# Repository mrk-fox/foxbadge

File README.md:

# foxbadge
My Fallout Badge (@Hack Club)

by
@scharonowmark

## Project Description
The project presented in this Repository is a versatile "Hacker-Badge" which has the following features:
1. Seeeduino XIAO ESP32-C6 as the main processor
2. A 4-mechanical switch (Cherry MX) controll
3. A 1.9 inch TFT screen
4. A battery system (NO BMS! ONLY BATTERIES WITH INTEGRATED BMS ARE SAFTE TO USE)
5. Supports 2 diffrent kind of lanyards
6. A case!

## BOM  

| id | Name                           | Qty | Price |   |
|----|--------------------------------|-----|-------|---|
| 1  | PCB                            | 1   | 2$    |   |
| 2  | Seeeduino XIAO ESP32-C6        | 1   |       |   |
| 3  | 1.9 inch TFT screen (8-pin)    | 1   |       |   |
| 4  | Cherry MX Low Profile Switches | 4   |       |   |
| 5  | 3D-Printed Case                | 1   |       |   |
| 6  | LiPo Battery (3.7v)            | 1   |       |   |

# Pictures

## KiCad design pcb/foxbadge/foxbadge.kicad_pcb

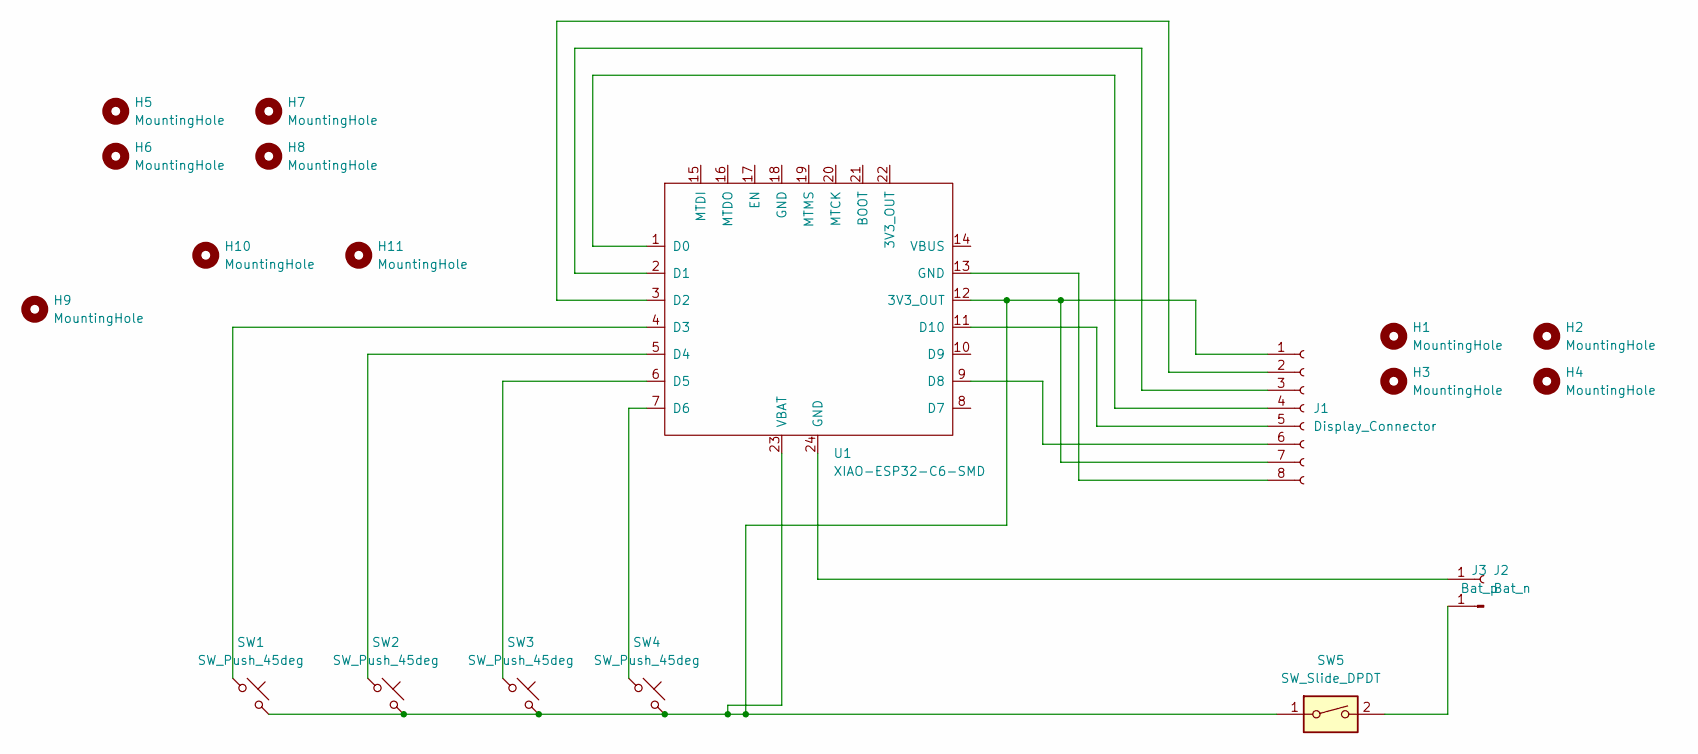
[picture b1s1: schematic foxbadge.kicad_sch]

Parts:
H1, H2, H3, H4: MountingHole; MountingHole_2.1mm
H5, H6, H7, H8: MountingHole; MountingHole_4mm
H9: MountingHole; MountingHole_6mm
H10, H11: MountingHole; MountingHole_3mm
J1: Display_Connector; PinSocket_1x08_P2.54mm_Vertical
J2: Bat_n; PinSocket_1x01_P2.54mm_Horizontal
J3: Bat_p; PinHeader_1x01_P2.54mm_Horizontal
SW1, SW2, SW3, SW4: SW_Push_45deg; SW_Cherry_MX_1.00u_PCB
SW5: SW_Slide_DPDT; SW_Slide_SPDT_Angled_CK_OS102011MA1Q
U1: XIAO-ESP32-C6-SMD

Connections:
unnamed: J1.1, J1.7, SW1.2, SW2.2, SW3.2, SW4.2, SW5.1, U1.12 (3V3_OUT), U1.23 (VBAT)
unnamed: J1.2, U1.3 (D2)
unnamed: J1.3, U1.2 (D1)
unnamed: J1.4, U1.1 (D0)
unnamed: J1.5, U1.11 (D10)
unnamed: J1.6, U1.9 (D8)
unnamed: J1.8, U1.13 (GND)
unnamed: J2.1 (Pin_1_1), U1.24 (GND)
unnamed: J3.1 (Pin_1_1), SW5.2
unnamed: SW1.1, U1.4 (D3)
unnamed: SW2.1, U1.5 (D4)
unnamed: SW3.1, U1.6 (D5)
unnamed: SW4.1, U1.7 (D6)

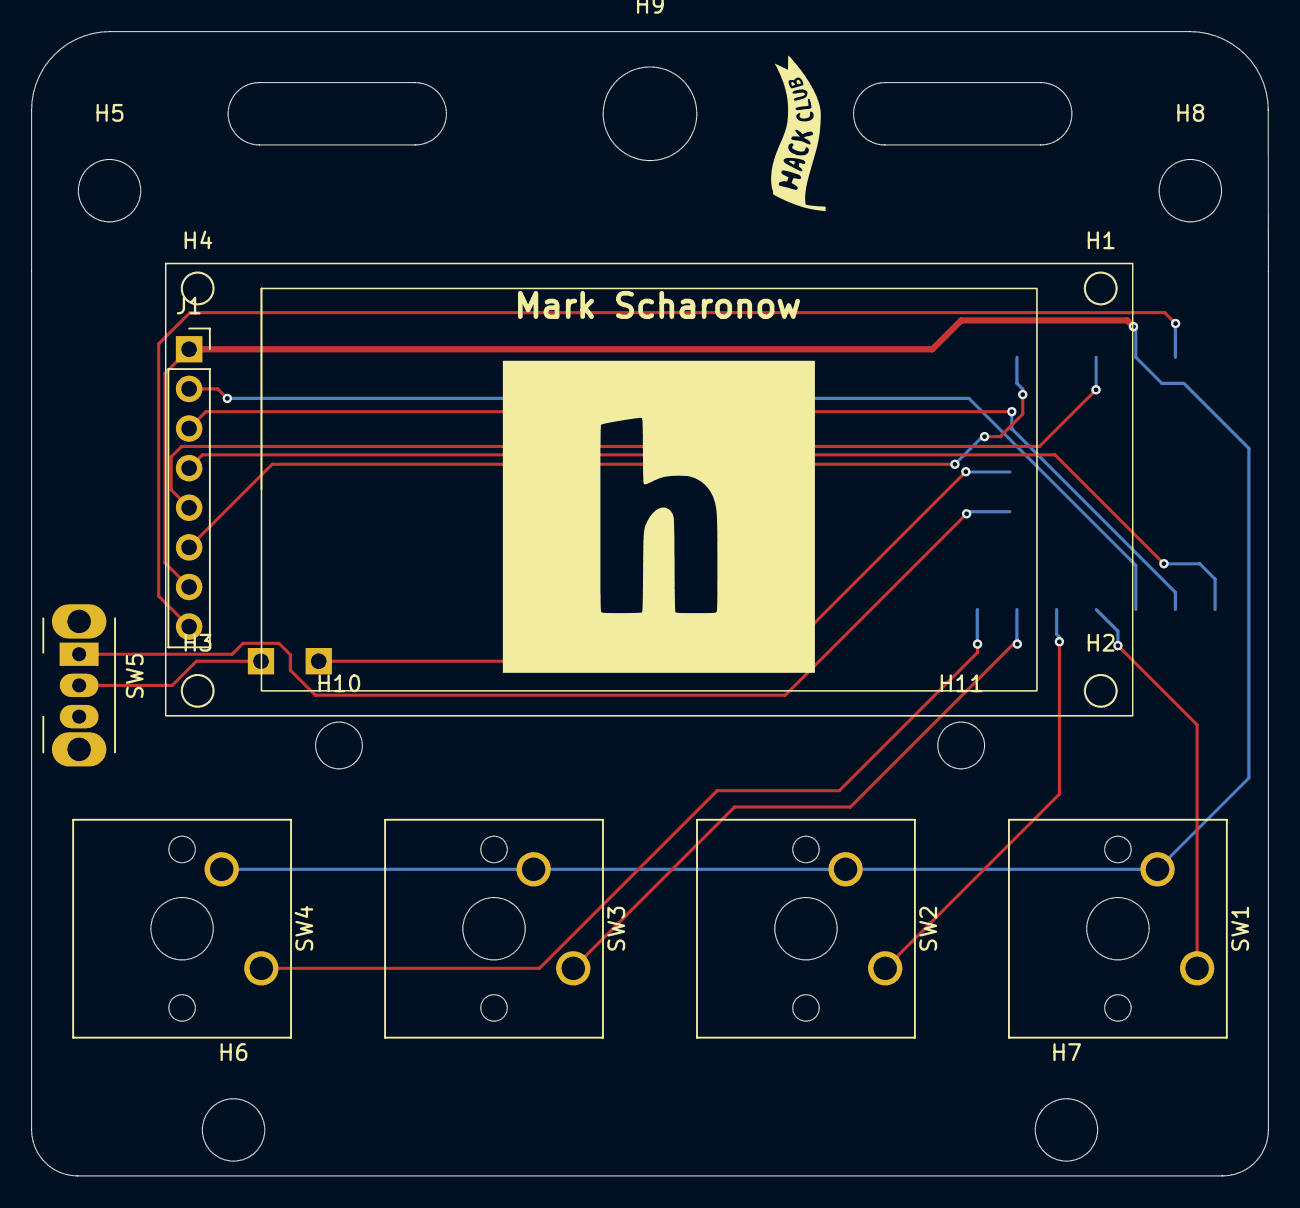
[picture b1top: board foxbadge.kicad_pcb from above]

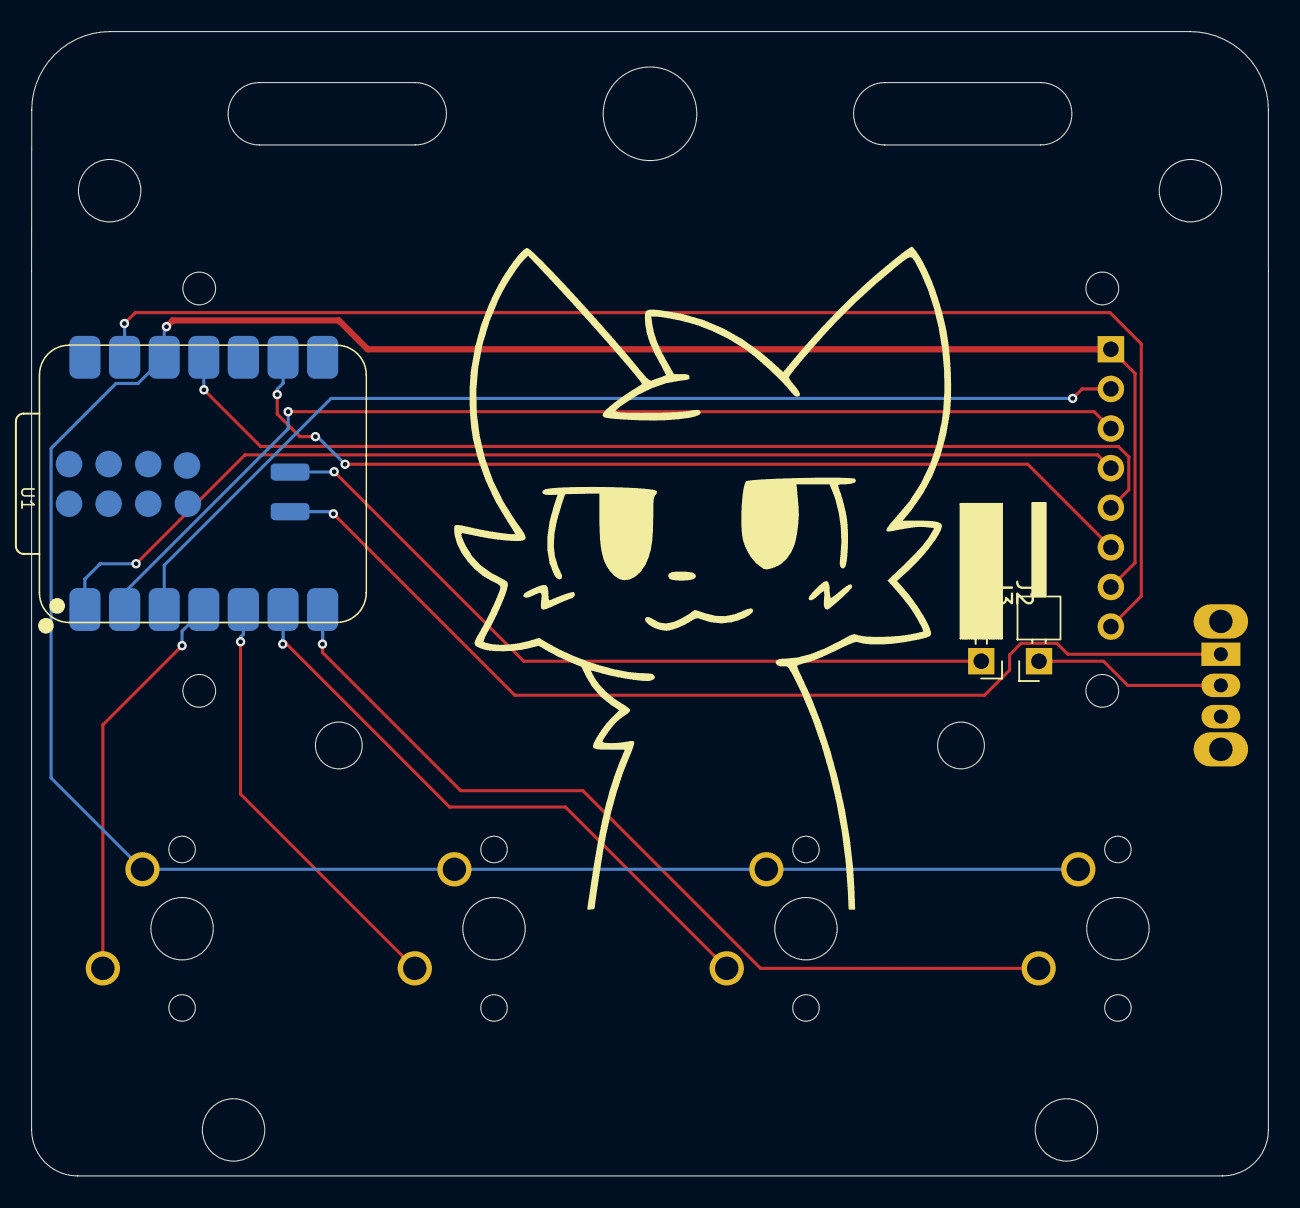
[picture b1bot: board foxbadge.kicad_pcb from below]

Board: 2 copper layers, 79.3 x 73.4 mm, 20 parts (3 on the bottom side), 13 nets.

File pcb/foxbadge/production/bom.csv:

Designator,Footprint,Quantity,Value,LCSC Part #
J1,PinSocket_1x08_P2.54mm_Vertical,1,Display_Connector,
J2,PinSocket_1x01_P2.54mm_Horizontal,1,Bat_n,
J3,PinHeader_1x01_P2.54mm_Horizontal,1,Bat_p,
"SW1, SW2, SW3, SW4",SW_Cherry_MX_1.00u_PCB,4,SW_Push_45deg,
SW5,SW_Slide_SPDT_Angled_CK_OS102011MA1Q,1,SW_Slide_DPDT,
U1,XIAO-ESP32-C6-SMD,1,XIAO-ESP32-C6-SMD,
